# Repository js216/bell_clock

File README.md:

# Alarm clock with a real bell

These are the design files for a simple three-button alarm clock.

- `3d`: FreeCAD files for custom-fabricated parts
- `firmware`: code that runs on the clock Arduino
- `pcb`: KiCad files for the clock motherboard
- `top_plate`: KiCad files for the "front panel"

### Using the clock

#### Turning alarms on/off

Next to the time display, there are three buttons, each with an LED above it
associated with one of the three possible alarms.

A short press on these buttons cycles between three alarm modes for each of the
three alarms: alarm (and LED) off; single-chime mode (LED glows red); continuous
chime mode (LED glows green).

#### Setting the time

Pressing the first two buttons (i.e., left and middle button) simultaneously,
the time display begins flashing, signifying we're now in time setting mode. The
left button increments hours, the middle button increments minutes (resetting
seconds whenever it is pressed), and the right button is the "enter" button,
accepting the new time value.

#### Showing seconds

Pressing the middle and right buttons simultaneously, the display changes from
the usual HH:MM to MM:SS for five seconds.

#### Offset correction

The clock crystal is not perfect, and can be either fast or slow. To correct for
that, it is possible to either add or drop seconds periodically.

To enter the offset correction mode, press all three buttons simultaneously. The
display begins flashing very quickly, signifying we're in offset correction
mode. Left decrements the value, the middle button increments the value, and the
right button accepts the value.

The meaning of the offset value is as follows. For positive values, the time is
moved forward by a second every 433 minutes multiplied by the value. For
negative values, the time is moved backwards (i.e., the clock is slowed down) by
one second every 433 minutes multiplied by the absolute value of the offset
correction setting.

For example, if the offset correction value is set to -5, this means that every
5 times 433 minutes (approx 72.17 hours) a second is lost.

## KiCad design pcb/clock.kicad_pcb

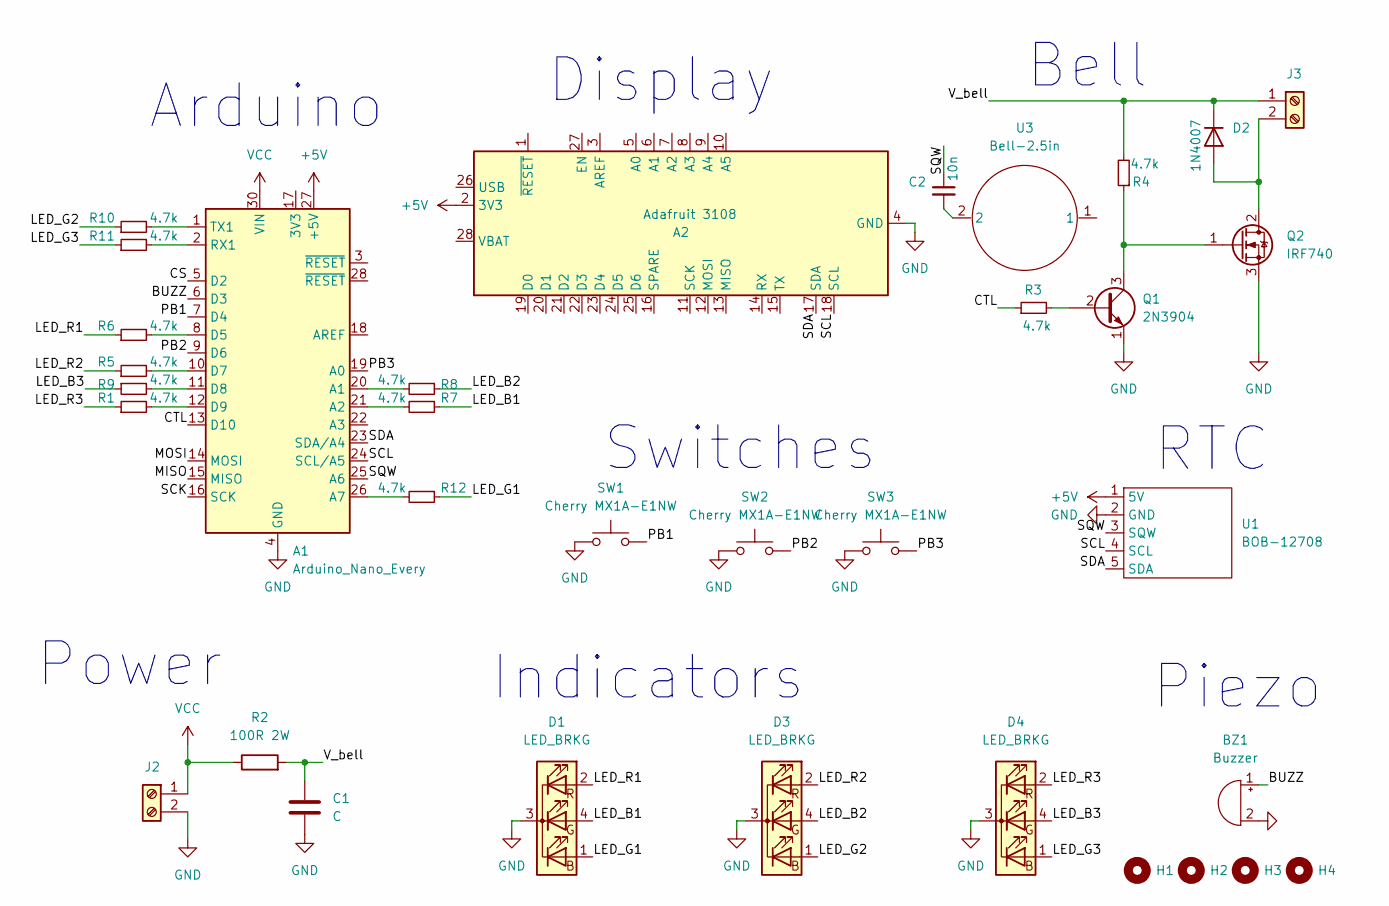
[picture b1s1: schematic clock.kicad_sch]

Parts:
A1: Arduino_Nano_Every; Arduino_Nano
A2: Adafruit 3108; Adafruit_Feather
BZ1: Buzzer; CP_Radial_Tantal_D10.5mm_P5.00mm
C1: C; CP_Radial_D10.0mm_P5.00mm
C2: 10n; CP_Axial_L10.0mm_D4.5mm_P15.00mm_Horizontal
D1, D3, D4: LED_BRKG; LED_D5.0mm-4_RGB
D2: 1N4007; D_DO-41_SOD81_P10.16mm_Horizontal
H1, H2, H3, H4: MountingHole; MountingHole_3.2mm_M3
J2, J3: Screw_Terminal_01x02; TerminalBlock_bornier-2_P5.08mm
Q1: 2N3904; TO-92_Inline
Q2: IRF740; TO-220-3_Horizontal_TabDown
R1, R3, R4, R5, R6, R7, R8, R9, R11, R12: 4.7k; R_Axial_DIN0207_L6.3mm_D2.5mm_P10.16mm_Horizontal
R2: 100R 2W; R_Axial_DIN0414_L11.9mm_D4.5mm_P15.24mm_Horizontal
R10: 4.7k; R_Axial_DIN0207_L6.3mm_D2.5mm_P7.62mm_Horizontal
SW1, SW2, SW3: Cherry MX1A-E1NW; SW_Cherry_MX_1.00u_PCB
U1: BOB-12708
U3: Bell-2.5in

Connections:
+5V: A1.27 (+5V), A2.2 (3V3), U1.1 (5V)
/BUZZ: A1.6 (D3), BZ1.1 (-)
/CS: A1.5 (D2)
/CTL: A1.13 (D10), R3.1
/LED_B1: D1.4 (GA), R7.1
/LED_B2: D3.4 (GA), R8.1
/LED_B3: D4.4 (GA), R9.1
/LED_G1: D1.1 (BA), R12.1
/LED_G2: D3.1 (BA), R10.1
/LED_G3: D4.1 (BA), R11.1
/LED_R1: D1.2 (RA), R6.1
/LED_R2: D3.2 (RA), R5.1
/LED_R3: D4.2 (RA), R1.1
/MISO: A1.15 (MISO)
/MOSI: A1.14 (MOSI)
/PB1: A1.7 (D4), SW1.2
/PB2: A1.9 (D6), SW2.2
/PB3: A1.19 (A0), SW3.2
/SCK: A1.16 (SCK)
/SCL: A1.24 (SCL/A5), A2.18 (SCL), U1.4 (SCL)
/SDA: A1.23 (SDA/A4), A2.17 (SDA), U1.5 (SDA)
/SQW: A1.25 (A6), C2.1, U1.3 (SQW)
/V_bell: C1.1, D2.1 (K), J3.1, R2.2, R4.2
GND: A1.4 (GND), A1.29 (GND), A2.4 (GND), BZ1.2 (+), C1.2, D1.3 (K), D3.3 (K), D4.3 (K), J2.2, Q1.1 (E), Q2.3 (S), SW1.1, SW2.1, SW3.1, U1.2 (GND)
unnamed: A1.1 (TX1), R10.2
unnamed: A1.2 (RX1), R11.2
unnamed: A1.8 (D5), R6.2
unnamed: A1.10 (D7), R5.2
unnamed: A1.11 (D8), R9.2
unnamed: A1.12 (D9), R1.2
unnamed: A1.20 (A1), R8.2
unnamed: A1.21 (A2), R7.2
unnamed: A1.26 (A7), R12.2
unnamed: C2.2, U3.2
unnamed: D2.2 (A), J3.2, Q2.2 (D)
unnamed: Q1.2 (B), R3.2
unnamed: Q1.3 (C), Q2.1 (G), R4.1
VCC: A1.30 (VIN), J2.1, R2.1

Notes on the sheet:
Bell
Switches
RTC
Indicators
Display
Piezo
Power
Arduino

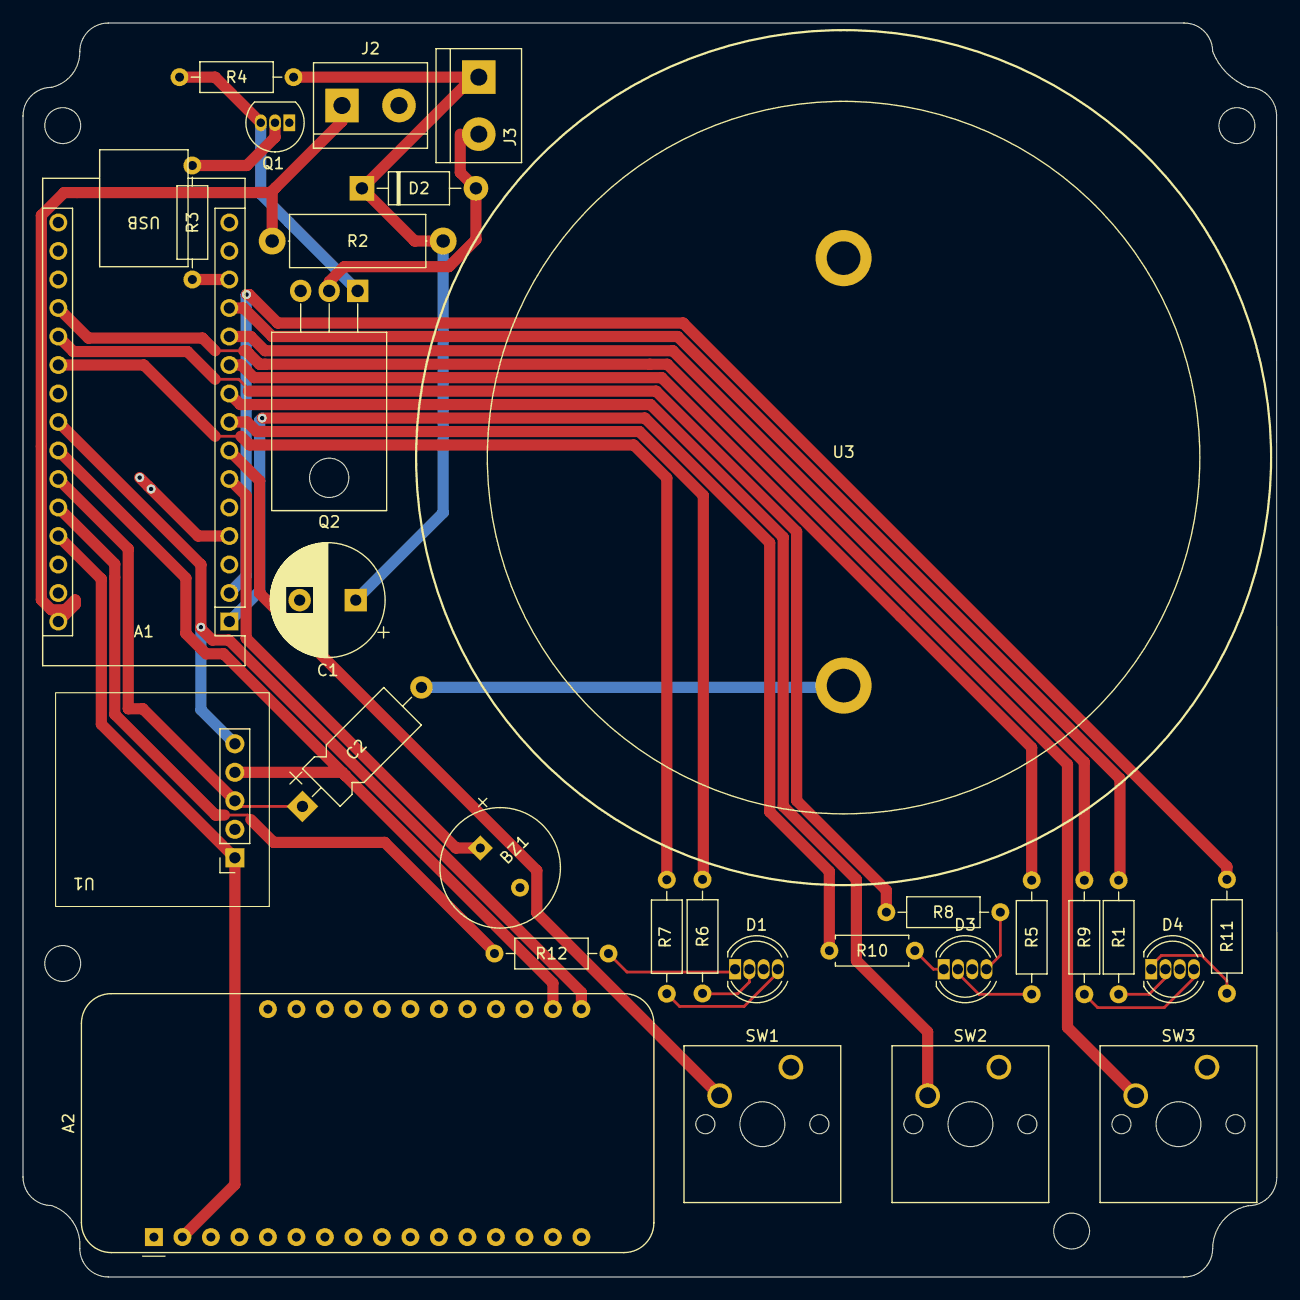
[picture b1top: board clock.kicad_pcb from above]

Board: 2 copper layers, 111.7 x 111.8 mm, 34 parts (0 on the bottom side), 34 nets.

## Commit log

2024-12-12 add clock image
2024-12-13 more info
